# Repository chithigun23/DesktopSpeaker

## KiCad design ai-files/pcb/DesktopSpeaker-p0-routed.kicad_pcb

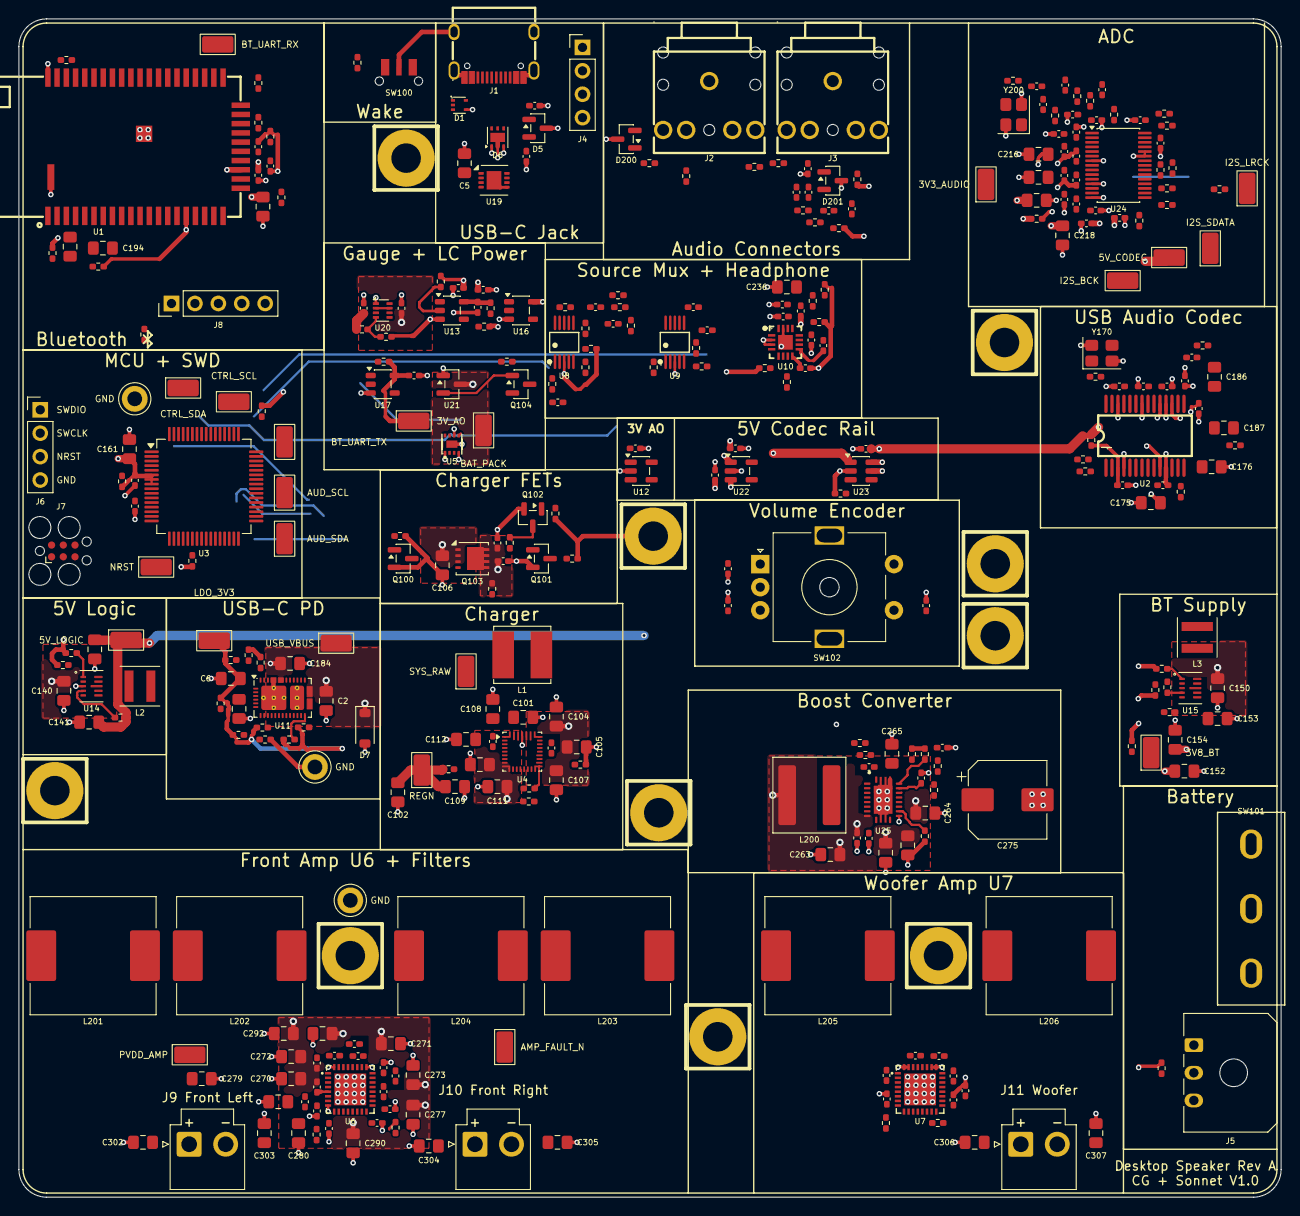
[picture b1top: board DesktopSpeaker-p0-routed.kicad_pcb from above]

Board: 4 copper layers, 136.9 x 127.8 mm, 351 parts (1 on the bottom side), 208 nets.

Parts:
C2, C5: 4.7uF X7R 50V; C_0805_2012Metric_Pad1.18x1.45mm_HandSolder
C6: 22uF X7R 10V; C_0805_2012Metric_Pad1.18x1.45mm_HandSolder
C100, C101, C108, C111, C112: 10uF / 50V; C_0805_2012Metric_Pad1.18x1.45mm_HandSolder
C102, C109: 10uF / 10V; C_0805_2012Metric_Pad1.18x1.45mm_HandSolder
C103, C110: 47nF / 50V; C_0402_1005Metric_Pad0.74x0.62mm_HandSolder
C104, C105, C106, C107: 22uF / 10V; C_0805_2012Metric_Pad1.18x1.45mm_HandSolder
C120: 100nF X7R 10V; C_0402_1005Metric_Pad0.74x0.62mm_HandSolder
C122, C123, C124, C125: 1uF X5R 16V; C_0402_1005Metric_Pad0.74x0.62mm_HandSolder
C126, C130, C131, C132, C160, C162, C191, C213, C215, C217, C219, C237, C238, C246, C260, C267, C276, C278, C281, C289, C291, C294: 100nF; C_0402_1005Metric_Pad0.74x0.62mm_HandSolder
C140, C141, C142, C150, C152, C153, C154: 22uF 10V X7R; C_0805_2012Metric_Pad1.18x1.45mm_HandSolder
C161, C186, C187, C194, C195, C236, C280, C293: 4.7uF; C_0805_2012Metric_Pad1.18x1.45mm_HandSolder
C170, C171, C172, C173, C174, C192, C193, C212, C220, C221, C222, C224, C225, C230, C231, C232, C233, C234, C235, C239, C240, C241, C245, C282, C283, C284, C295, C296, C297: 1uF; C_0402_1005Metric_Pad0.74x0.62mm_HandSolder
C175, C176, C190, C214, C216, C218, C223: 10uF; C_0805_2012Metric_Pad1.18x1.45mm_HandSolder
C177, C178: 33pF; C_0402_1005Metric_Pad0.74x0.62mm_HandSolder
C181: 10uF X7R 10V; C_0805_2012Metric_Pad1.18x1.45mm_HandSolder
C182: 330pF C0G CC1 filter; C_0402_1005Metric_Pad0.74x0.62mm_HandSolder
C183: 330pF C0G CC2 filter; C_0402_1005Metric_Pad0.74x0.62mm_HandSolder
C184: 1uF X7R 50V; C_0805_2012Metric_Pad1.18x1.45mm_HandSolder
C200, C201, C202, C203, C204, C205, C243, C244: 2.2uF; C_0402_1005Metric_Pad0.74x0.62mm_HandSolder
C206, C207, C208, C209, C210, C211: 10nF C0G; C_0402_1005Metric_Pad0.74x0.62mm_HandSolder
C226, C227: 22pF C0G; C_0402_1005Metric_Pad0.74x0.62mm_HandSolder
C261, C262, C263, C264: 22uF 10V; C_0805_2012Metric_Pad1.18x1.45mm_HandSolder
C265: 2.2uF; C_0805_2012Metric_Pad1.18x1.45mm_HandSolder
C266: 47nF; C_0402_1005Metric_Pad0.74x0.62mm_HandSolder
C268: 6.8nF; C_0402_1005Metric_Pad0.74x0.62mm_HandSolder
C269: 47pF; C_0402_1005Metric_Pad0.74x0.62mm_HandSolder
C270: 1uF; C_0805_2012Metric_Pad1.18x1.45mm_HandSolder
C271, C272, C273, C274, C277, C279, C290, C292: 22uF 25V; C_0805_2012Metric_Pad1.18x1.45mm_HandSolder
C275: 100uF 25V; CP_Elec_8x10
C285, C286, C287, C288, C298, C299, C300, C301: 0.47uF; C_0402_1005Metric_Pad0.74x0.62mm_HandSolder
C302, C303, C304, C305, C306, C307: 0.68uF 50V; C_0805_2012Metric_Pad1.18x1.45mm_HandSolder
C308, C309, C310: 10nF; C_0402_1005Metric_Pad0.74x0.62mm_HandSolder
D1: TPD2E2U06DRLR
D5: ESDA25L
D6: TVS2200DRVR
D7: 1N5819HW; PD_D_SOD123
D200, D201: PESD5V0S2BT
FB200: BLM15AG601SN1D; R_0402_1005Metric_Pad0.72x0.64mm_HandSolder
H1, H2, H3, H4, H5, H6, H7, H9: M3 PTH GND; MountingHole_3.2mm_M3_PTH_GND
HA1, HA2: M3 PTH GND; MountingHole_3.2mm_M3_PTH_GND
J1: USB_C_Receptacle_USB2.0_16P; TYPE-C-31-M-12
J2: HEAD_OUT; PJ-307
J3: AUX_IN; PJ-307
J4: I2C service; PD_SERVICE_HDR
J5: 1S_PACK_3PIN; Molex_Micro-Fit_3.0_43650-0300_1x03_P3.00mm_Horizontal
J6: SWD; PinHeader_1x04_P2.54mm_Vertical
J7: SWD_TC2030; Tag-Connect_TC2030-IDC-FP_2x03_P1.27mm_Vertical
J8: BM83_PROG; PinHeader_1x05_P2.54mm_Vertical
J9, J10, J11: B2P-VH; JST_B2P_VH_1x02_P3.96mm_Vertical
L1: 2.2uH; Bourns_SRN6045TA-2R2Y
L2, L3: 0.47uH; Coilcraft_XFL4015-471MEC
L200: 2.2uH; L_Coilcraft_XAL7070-XXX
L201, L202, L203, L204, L205, L206: 22uH; L_Sunlord_MWSA1265S
LOGO1: Orwellian Industries; Logo_Orwellian
Q100, Q101, Q102, Q104: 2N7002
Q103: CSD17579Q3A; CSD17579Q3A_DNH0008A
R10: 200k 1%; R_0402_1005Metric_Pad0.72x0.64mm_HandSolder
R11, R13, R14, R15, R18: 10k 1%; R_0402_1005Metric_Pad0.72x0.64mm_HandSolder
R12, R16, R17: 100k 1%; R_0402_1005Metric_Pad0.72x0.64mm_HandSolder
R100: 5.23k; R_0402_1005Metric_Pad0.72x0.64mm_HandSolder
R101: 30.1k; R_0402_1005Metric_Pad0.72x0.64mm_HandSolder
R102, R120, R121: 4.7k; R_0402_1005Metric_Pad0.72x0.64mm_HandSolder
R103, R107, R109, R110, R111, R113, R125, R142, R152, R153, R154, R160, R175, R176, R180, R181, R184, R211, R212, R220, R221, R222, R223, R224, R225, R234, R235, R236, R237, R238, R239, R255, R259: 100k; R_0402_1005Metric_Pad0.72x0.64mm_HandSolder
R106, R182, R183, R242, R243, R244, R262: 10k; R_0402_1005Metric_Pad0.72x0.64mm_HandSolder
R108, R124: 180k; R_0402_1005Metric_Pad0.72x0.64mm_HandSolder
R112: 100R; R_0402_1005Metric_Pad0.72x0.64mm_HandSolder
R122, R232, R233: 47k; R_0402_1005Metric_Pad0.72x0.64mm_HandSolder
R126, R127, R174, R241: 1M; R_0402_1005Metric_Pad0.72x0.64mm_HandSolder
R140: 78.7k 1%; R_0402_1005Metric_Pad0.72x0.64mm_HandSolder
R141: 9.1k 1%; R_0402_1005Metric_Pad0.72x0.64mm_HandSolder
R150: 604k 1%; R_0402_1005Metric_Pad0.72x0.64mm_HandSolder
R151: 91k 1%; R_0402_1005Metric_Pad0.72x0.64mm_HandSolder
R170: 2.2; R_0402_1005Metric_Pad0.72x0.64mm_HandSolder
R171, R172: 22; R_0402_1005Metric_Pad0.72x0.64mm_HandSolder
R173: 1.5k; R_0402_1005Metric_Pad0.72x0.64mm_HandSolder
R185, R186, R187, R226, R227, R228, R229, R230, R231, R240, R257, R258, R261: 1k; R_0402_1005Metric_Pad0.72x0.64mm_HandSolder
R200, R201, R202, R203, R204, R205: 100; R_0402_1005Metric_Pad0.72x0.64mm_HandSolder
R206, R207, R208: 33; R_0402_1005Metric_Pad0.72x0.64mm_HandSolder
R209, R210: 2.2k; R_0402_1005Metric_Pad0.72x0.64mm_HandSolder
R250: 499k; R_0402_1005Metric_Pad0.72x0.64mm_HandSolder
R251: 56k; R_0402_1005Metric_Pad0.72x0.64mm_HandSolder
R252: 301k; R_0402_1005Metric_Pad0.72x0.64mm_HandSolder
R253: 150k; R_0402_1005Metric_Pad0.72x0.64mm_HandSolder
R254: 82k; R_0402_1005Metric_Pad0.72x0.64mm_HandSolder
R256: 0R DNP; R_0402_1005Metric_Pad0.72x0.64mm_HandSolder
SW100: WAKE_QON; TE_1977066-1_Tact_RA_SMD
SW101: BAT_DISCONNECT; SHOUHAN_KCD1-201-R_Rocker_D20_Panel
SW102: EC11E; RotaryEncoder_Alps_EC11E-Switch_Vertical_H20mm_MountingHoles
TP1: USB_VBUS; TestPoint_Keystone_5015_Micro_Mini
TP2: SYS_RAW; TestPoint_Keystone_5015_Micro_Mini
TP3: BAT_PACK; TestPoint_Keystone_5015_Micro_Mini
TP4: 3V_AO; TestPoint_Keystone_5015_Micro_Mini
TP5: LDO_3V3; TestPoint_Keystone_5015_Micro_Mini
TP6: 3V3_AUDIO; TestPoint_Keystone_5015_Micro_Mini
TP7: 5V_LOGIC; TestPoint_Keystone_5015_Micro_Mini
TP8: 5V_CODEC; TestPoint_Keystone_5015_Micro_Mini
TP9: 3V8_BT; TestPoint_Keystone_5015_Micro_Mini
TP10: PVDD_AMP; TestPoint_Keystone_5015_Micro_Mini
TP11: REGN; TestPoint_Keystone_5015_Micro_Mini
TP12: I2S_BCK; TestPoint_Keystone_5015_Micro_Mini
TP13: I2S_LRCK; TestPoint_Keystone_5015_Micro_Mini
TP14: I2S_SDATA; TestPoint_Keystone_5015_Micro_Mini
TP15: CTRL_SDA; TestPoint_Keystone_5015_Micro_Mini
TP16: CTRL_SCL; TestPoint_Keystone_5015_Micro_Mini
TP17: AUD_SDA; TestPoint_Keystone_5015_Micro_Mini
TP18: AUD_SCL; TestPoint_Keystone_5015_Micro_Mini
TP19: NRST; TestPoint_Keystone_5015_Micro_Mini
TP20: AMP_FAULT_N; TestPoint_Keystone_5015_Micro_Mini
TP21: BT_UART_TX; TestPoint_Keystone_5015_Micro_Mini
TP22: BT_UART_RX; TestPoint_Keystone_5015_Micro_Mini
TP23, TP24, TP25: GND; TestPoint_Keystone_5010-5014_Multipurpose
U1: BM83SM1-00TA
U2: PCM2902CDBR
U3: STM32G071RBT6
U4: BQ25792RQMR
U5: MAX17048G+T10
U6, U7: TAS5825MRHBR
U8, U9: TS5A23157DGSR
U10: TPA6132A2RTER
U11: TPS25730DREFR; TPS25730D
U12: TPS7A0230PDBVR
U13, U16, U17: TS5A3167DBVR
U14, U15: TPS63802DLAR
U19: TPS7B8450QWDRBRQ1; TPS7B8450QWDRBRQ1_WSON-8
U20: TPS2116DRLR
U21: TPS3839G33DBZR
U22: TPS7A2033PDBVR
U23: TPS22917DBVR
U24: PCM1862DBTR
U25: TPS61088RHLR
Y170: 12MHz; Crystal_SMD_3225-4Pin_3.2x2.5mm
Y200: 24.576MHz; Crystal_SMD_3225-4Pin_3.2x2.5mm

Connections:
/3V3_AUDIO: C217.1, C218.1, C219.1, C220.1, C222.1, C223.1, C237.1, C238.1, C241.1, C280.1, C281.1, C293.1, C294.1, FB200.1, R209.1, R210.1, R232.1, R239.1, R262.1, TP6.1, U6.6, U7.6, U8.8, U9.8, U10.14, U22.5, U24.13, U24.14
/3V8_BT: C152.1, C153.1, C154.1, C190.1, C191.1, R150.1, R154.1, TP9.1, U1.23, U15.6
/3V_AO: C123.1, C130.1, C131.1, C132.1, C160.1, C161.1, J7.1, R106.1, R120.1, R121.1, R122.1, R126.1, R241.1, TP4.1, U3.6, U3.7, U3.8, U12.5, U13.5, U16.5, U17.5
/5V_CODEC: C225.1, R170.1, TP8.1, U23.5, U23.6
/5V_LOGIC: C141.1, C142.1, C221.1, C224.1, R140.1, TP7.1, U14.6, U22.1, U22.3, U23.1
/5V_LOGIC_EN: R142.1, U3.59, U14.1
/ADC_INT: R211.1, U3.26, U24.21
/AMP_BOOST_EN: R255.1, U3.24, U25.2
/AMP_FAULT_N: R262.2, TP20.1, U3.25, U6.9, U7.9
/AMP_PDN: R257.1, R258.1, R259.1, U3.23
/AUD_SCL: R209.2, TP18.1, U3.30, U6.16, U7.16, U24.24
/AUD_SDA: R210.2, TP17.1, U3.31, U6.15, U7.15, U24.23
/AUX_DET: R242.2, U3.29
/AUX_L: C204.1, C234.1, D201.1, J3.5, R243.1
/AUX_R: C205.1, C235.1, D201.2, J3.2, R244.1
/Amplifiers/PVDD_AMP: C270.1, C271.1, C272.1, C273.1, C274.1, C275.1, C276.1, C277.1, C278.1, C279.1, C289.1, C290.1, C291.1, C292.1, R250.1, TP10.1, U6.3, U6.4, U6.21, U6.22, U7.3, U7.4, U7.21, U7.22, U25.14, U25.15, U25.16
/BT_AUDIO_L: C194.2, C202.1, C232.1, R180.1
/BT_AUDIO_R: C195.2, C203.1, C233.1, R181.1
/BT_FORCE_PWM: R153.1, U3.37, U15.2
/BT_MFB: R183.1, U3.57
/BT_PWR_EN: R152.1, U3.36, U15.1
/BT_RST_N: R185.1, U3.58
/BT_TX_IND: R187.2, U3.62
/BT_UART_RX: R186.2, TP22.1, U3.20
/BT_UART_TX: R182.1, TP21.1, U3.19
/Battery_Charger/BAT_INT: C106.1, Q103.1, Q103.2, Q103.3, U4.22, U4.23
/Battery_Charger/BTST1: C103.1, U4.4
/Battery_Charger/BTST2: C110.1, U4.19
/Battery_Charger/CE_N: Q100.3, R103.2, U4.13
/Battery_Charger/ILIM_HIZ: Q101.3, R108.2, R109.1, U4.17
/Battery_Charger/PACK_RAW: J5.1, SW101.2
/Battery_Charger/PMID: C101.1, C108.1, C112.1, U4.29
/Battery_Charger/PROG: R102.1, U4.20
/Battery_Charger/REGN: C102.1, C109.1, R100.1, R103.1, R108.1, R110.1, TP11.1, U4.5
/Battery_Charger/SW1: C103.2, L1.1, U4.28
/Battery_Charger/SW2: C110.2, L1.2, U4.26
/Battery_Charger/TS_SENSE: J5.2, R100.2, R101.1, U4.16
/Battery_Charger/VBUS_PD: C100.1, C111.1, U4.2, U4.3, U4.8, U4.9, U11.20
/Bluetooth/BT_RST_M: J8.1, R185.2, U1.43
/Bluetooth/BT_RXD_M: J8.3, R182.2, U1.29
/Bluetooth/BT_SYS_CFG: J8.2, U1.31
/Bluetooth/BT_TXD_M: J8.4, R186.1, U1.30
/CHG_ENABLE: Q100.1, R107.1, U3.38
/CHG_INT: R106.2, U3.5, U4.21
/CHG_QON_SENSE: R113.2, U3.3
/CHG_SYS_ENABLE: Q102.1, R111.1, U3.42
/CODEC_PWR_EN: R212.1, U3.39, U23.3
/CTRL_SCL: R120.2, TP16.1, U3.60, U4.14, U16.2
/CTRL_SDA: R121.2, TP15.1, U3.61, U4.15, U13.2
/Fuel_Gauge_Power/BAT_PACK: C120.1, C126.1, Q103.5, Q103.6, Q103.7, Q103.8, Q103.9, R112.1, SW101.1, TP3.1, U5.3, U21.3
/Fuel_Gauge_Power/GAUGE_ISO_N: Q104.3, R126.2, U13.4, U16.4, U17.4
/Fuel_Gauge_Power/USB_AUX_5V: C5.1, C124.1, R124.1, U19.1, U20.3, U20.5
/GAUGE_ALRT_N: R122.2, U3.17, U17.2
/HP_DET: R240.2, U3.28
/HP_EN: R236.1, U3.15, U10.13
/HP_G0: R237.1, U3.16, U10.6
/HP_G1: R238.1, U3.21, U10.7
/HP_SEL_A: R234.1, U3.13, U8.1, U8.5
/HP_SEL_B: R235.1, U3.14, U9.1, U9.5
/Headphone_Aux/AUX_TIPSW: C246.1, J3.4, R241.2, R242.1
/Headphone_Aux/HP_L: C239.1, U9.10
/Headphone_Aux/HP_OUTL: D200.1, J2.5, U10.16
/Headphone_Aux/HP_OUTR: D200.2, J2.2, U10.5
/Headphone_Aux/HP_R: C240.1, U9.6
/Headphone_Aux/HP_TIPSW: J2.4, R239.2, R240.1
/Headphone_Aux/VMID_HP: C236.1, R220.2, R221.2, R222.2, R223.2, R224.2, R225.2, R232.2, R233.1
/I2S_BCK: R207.2, TP12.1, U6.13, U7.13
/I2S_LRCK: R208.2, TP13.1, U6.12, U7.12
/I2S_SDATA: R206.2, TP14.1, U6.14, U7.14
/MCU/ENC_A: C308.1, SW102.A, U3.48
/MCU/ENC_B: C309.1, SW102.B, U3.49
/MCU/ENC_SW: C310.1, SW102.S1, U3.64
/MCU/NRST: C162.1, J6.3, J7.3, TP19.1, U3.12
/MCU/SWCLK: J6.2, J7.4, R160.1, U3.46
/MCU/SWDIO: J6.1, J7.2, U3.45
/PDCTRL_SCL: J4.2, R15.2, U3.43, U11.9
/PDCTRL_SDA: J4.3, R14.2, U3.44, U11.8
/PD_PLUG_EVENT: R16.1, U3.4, U11.37
/PD_SINK_EN: R17.2, U3.63, U11.19
/SYS_RAW: C104.1, C105.1, C107.1, C125.1, C140.1, C150.1, C260.1, C261.1, C262.1, C263.1, C264.1, L200.1, TP2.1, U4.25, U14.2, U14.10, U15.10, U20.6, U25.9
/USB_AUDIO_L: C186.2, C200.1, C230.1, R175.1
/USB_AUDIO_R: C187.2, C201.1, C231.1, R176.1
/USB_CC1: C182.1, D5.1, J1.A5, U11.28
/USB_CC2: C183.1, D5.2, J1.B5, U11.29
/USB_DN: D1.5, J1.A7, J1.B7, R172.1
/USB_DP: D1.3, J1.A6, J1.B6, R171.1, R173.1
/USB_PD/LDO_1V5: C181.1, U11.4
/USB_PD/LDO_3V3: C6.1, J4.1, R10.1, R13.1, R14.1, R15.1, R16.2, R17.1, TP5.1, U11.1, U11.3
/USB_PD/VIN_LOW: R12.1, U11.38
/USB_VBUS: C2.1, C184.1, D6.4, D6.5, D6.6, D7.1, J1.A4B9, J1.B4A9, TP1.1, U11.23, U11.32, U19.7, U19.8
GND: C2.2, C5.2, C6.2, C100.2, C101.2, C102.2, C104.2, C105.2, C106.2, C107.2, C108.2, C109.2, C111.2, C112.2, C120.2, C122.2, C123.2, C124.2, C125.2, C126.2, C130.2, C131.2, C132.2, C140.2, C141.2, C142.2, C150.2, C152.2, C153.2, C154.2, C160.2, C161.2, C162.2, C170.2, C171.2, C172.2, C173.2, C174.2, C175.2, C176.2, C177.2, C178.2, C181.2, C182.2, C183.2, C184.2, C190.2, C191.2, C192.2, C193.2, C206.2, C207.2, C208.2, C209.2, C210.2, C211.2, C212.2, C213.2, C214.2, C215.2, C216.2, C217.2, C218.2, C219.2, C220.2, C221.2, C222.2, C223.2, C224.2, C225.2, C226.2, C227.2, C236.2, C237.2, C238.2, C241.2, C243.2, C244.2, C246.2, C260.2, C261.2, C262.2, C263.2, C264.2, C265.2, C266.2, C268.2, C269.2, C270.2, C271.2, C272.2, C273.2, C274.2, C275.2, C276.2, C277.2, C278.2, C279.2, C280.2, C281.2, C282.2, C283.2, C284.2, C289.2, C290.2, C291.2, C292.2, C293.2, C294.2, C295.2, C296.2, C297.2, C302.2, C303.2, C304.2, C305.2, C306.2, C307.2, C308.2, C309.2, C310.2, D1.4, D5.3, D6.1, D6.2, D6.3, D6.7, D7.2, D200.3, D201.3, H1.1, H2.1, H3.1, H4.1, H5.1, H6.1, H7.1, H9.1, HA1.1, HA2.1, J1.1, J1.2, J1.3, J1.4, J1.A1B12, J1.B1A12, J2.1, J3.1, J4.4, J5.3, J6.4, J7.5, J8.5, Q100.2, Q101.2, Q102.2, Q104.2, R11.2, R12.2, R18.2, R101.2, R102.2, R107.2, R109.2, R111.2, R125.2, R127.2, R141.2, R142.2, R151.2, R152.2, R153.2, R154.2, R160.2, R175.2, R176.2, R180.2, R181.2, R184.2, R211.2, R212.2, R233.2, R234.2, R235.2, R236.2, R237.2, R238.2, R243.2, R244.2, R251.2, R253.2, R255.2, R256.2, R259.2, R261.1, SW100.2, SW102.C, SW102.MP, SW102.S2, TP23.1, TP24.1, TP25.1, U1.16, U1.50, U1.56, U1.57, U2.4, U2.11, U2.18, U2.22, U2.26, U3.9, U4.10, U4.11, U4.27, U5.1, U5.4, U5.6, U5.9, U6.5, U6.8, U6.20, U6.25, U6.26, U6.31, U6.32, U6.33, U7.5, U7.20, U7.25, U7.26, U7.31, U7.32, U7.33, U8.3, U9.3, U10.2, U10.3, U10.10, U10.15, U10.17, U11.2, U11.5, U11.11, U11.12, U11.14, U11.16, U11.17, U11.26, U11.27, U11.31, U11.34, U11.39, U12.2, U13.3, U14.3, U14.8, U15.3, U15.8, U16.3, U17.3, U19.5, U19.9, U20.1, U21.1, U22.2, U23.2, U24.7, U24.12, U24.15, U24.25, U24.26, U25.11, U25.12, U25.20, U25.21, Y170.2, Y170.4, Y200.2, Y200.4
unnamed: C200.2, R200.1
unnamed: C201.2, R201.1
unnamed: C202.2, R202.1
unnamed: C203.2, R203.1
unnamed: C204.2, R204.1
unnamed: C205.2, R205.1
unnamed: C230.2, R220.1, R226.1
unnamed: C231.2, R221.1, R227.1
unnamed: C232.2, R222.1, R228.1
unnamed: C233.2, R223.1, R229.1
unnamed: C234.2, R224.1, R230.1
unnamed: C235.2, R225.1, R231.1
unnamed: C268.1, R254.2
unnamed: C302.1, J9.1, L201.2
unnamed: C303.1, J9.2, L202.2
unnamed: C304.1, J10.1, L203.2
unnamed: C305.1, J10.2, L204.2
unnamed: C306.1, J11.1, L205.2
unnamed: C307.1, J11.2, L206.2
unnamed: Q101.1, Q102.3, R110.2
unnamed: Q103.4, U4.24
unnamed: Q104.1, R127.1, U21.2
unnamed: R18.1, U11.36
unnamed: C194.1, U1.8
unnamed: C195.1, U1.6
unnamed: R187.1, U1.49
unnamed: R183.2, R184.1, U1.26
unnamed: C193.1, U1.24
unnamed: C192.1, U1.25
unnamed: R171.2, U2.1
unnamed: R172.2, U2.2
unnamed: C171.1, R173.2, U2.8, U2.9, U2.27
unnamed: C170.1, R170.2, U2.3
unnamed: C175.1, U2.10
unnamed: C174.1, U2.17
unnamed: C173.1, U2.19
unnamed: C172.1, U2.23
unnamed: C176.1, U2.14
unnamed: C186.1, U2.16
unnamed: C187.1, U2.15
unnamed: C177.1, R174.1, U2.21, Y170.1
unnamed: C178.1, R174.2, U2.20, Y170.3
unnamed: R112.2, U4.18
unnamed: R113.1, SW100.1, U4.12
unnamed: C284.1, U6.19
unnamed: C285.1, U6.1
unnamed: C286.2, U6.29
unnamed: C287.1, U6.24
unnamed: C288.2, U6.28
unnamed: C283.1, U6.18
unnamed: C285.2, L201.1, U6.2
unnamed: C286.1, L202.1, U6.30
unnamed: C287.2, L203.1, U6.23
unnamed: C288.1, L204.1, U6.27
unnamed: C282.1, U6.7
unnamed: R257.2, U6.17
unnamed: R261.2, U7.8
unnamed: C297.1, U7.19
unnamed: C298.1, U7.1
unnamed: C299.2, U7.29
unnamed: C300.1, U7.24
unnamed: C301.2, U7.28
unnamed: C296.1, U7.18
unnamed: C298.2, C299.1, L205.1, U7.2, U7.30
unnamed: C300.2, C301.1, L206.1, U7.23, U7.27
unnamed: C295.1, U7.7
unnamed: R258.2, U7.17
unnamed: U8.10, U9.9
unnamed: U8.6, U9.7
unnamed: R226.2, U8.9
unnamed: R227.2, U8.7
unnamed: R228.2, U8.2
unnamed: R229.2, U8.4
unnamed: R230.2, U9.2
unnamed: R231.2, U9.4
unnamed: C245.2, U10.9
unnamed: C245.1, U10.11
unnamed: C243.1, U10.12
unnamed: C244.1, U10.8
unnamed: C239.2, U10.1
unnamed: C240.2, U10.4
unnamed: R10.2, R11.1, U11.7
unnamed: R13.2, U11.18
unnamed: C122.1, U12.1, U12.3, U20.2, U20.7
unnamed: U5.8, U13.1
unnamed: R140.2, R141.1, U14.4
unnamed: L2.1, U14.9
unnamed: L2.2, U14.7
unnamed: R150.2, R151.1, U15.4
unnamed: L3.1, U15.9
unnamed: L3.2, U15.7
unnamed: U5.7, U16.1
unnamed: U5.5, U17.1
unnamed: R124.2, R125.1, U20.4
unnamed: C215.1, C216.1, FB200.2, U24.8
unnamed: R207.1, U24.17
unnamed: R206.1, U24.18
unnamed: C213.1, C214.1, U24.11
unnamed: R208.1, U24.16
unnamed: C206.1, R200.2, U24.3
unnamed: C208.1, R202.2, U24.1
unnamed: C210.1, R204.2, U24.29
unnamed: C207.1, R201.2, U24.4
unnamed: C209.1, R203.2, U24.2
unnamed: C211.1, R205.2, U24.30
unnamed: C212.1, U24.6
unnamed: C226.1, U24.10, Y200.1
unnamed: C227.1, U24.9, Y200.3
unnamed: C267.1, U25.8
unnamed: C269.1, R254.1, U25.18
unnamed: R250.2, R251.1, U25.17
unnamed: R252.1, U25.3
unnamed: R253.1, U25.19
unnamed: R256.1, U25.13
unnamed: C266.1, U25.10
unnamed: C267.2, L200.2, R252.2, U25.4, U25.5, U25.6, U25.7
unnamed: C265.1, U25.1

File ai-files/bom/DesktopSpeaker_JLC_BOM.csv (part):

Comment,Designator,Footprint,LCSC Part #,MPN,Manufacturer,Qty
4.7uF X7R 50V,"C2,C5",C_0805_2012Metric_Pad1.18x1.45mm_HandSolder,C5159426,C2012X7R1H475KT0A0E,TDK,2
22uF 10V X7R,"C6,C104,C105,C106,C107,C140,C141,C142,C150,C152,C153,C154,C261,C262,C263,C264",C_0805_2012Metric_Pad1.18x1.45mm_HandSolder,C907991,GRM21BZ71A226ME15L,Murata,16
10uF / 50V,"C100,C101,C108,C111,C112",C_0805_2012Metric_Pad1.18x1.45mm_HandSolder,C440198,GRM21BR61H106KE43L,Murata,5
10uF,"C102,C109,C175,C176,C181,C190,C214,C216,C218,C223",C_0805_2012Metric_Pad1.18x1.45mm_HandSolder,C32635,CL21B106KPQNNNE,Samsung Electro-Mechanics,10
47nF / 50V,"C103,C110,C266",C_0402_1005Metric_Pad0.74x0.62mm_HandSolder,C117757,GRM155R71H473KE14D,Murata,3
100nF,"C120,C126,C130,C131,C132,C160,C162,C191,C213,C215,C217,C219,C237,C238,C246,C260,C267,C276,C278,C281,C289,C291,C294,C311,C312,C313,C314",C_0402_1005Metric_Pad0.74x0.62mm_HandSolder,C77020,GRM155R71H104KE14D,Murata,27
1uF,"C122,C123,C124,C125,C170,C171,C172,C173,C174,C192,C193,C212,C220,C221,C222,C224,C225,C230,C231,C232,C233,C234,C235,C239,C240,C245,C282,C283,C284,C295,C296,C297",C_0402_1005Metric_Pad0.74x0.62mm_HandSolder,C29266,CL05A105KO5NNNC,Samsung Electro-Mechanics,32
4.7uF,"C161,C186,C187,C194,C195,C236,C280,C293",C_0805_2012Metric_Pad1.18x1.45mm_HandSolder,C1779,CL21A475KAQNNNE,Samsung Electro-Mechanics,8
33pF,"C177,C178",C_0402_1005Metric_Pad0.74x0.62mm_HandSolder,C5137486,FCC0402N330J500AT,FOJAN,2
330pF C0G CC1 filter,"C182,C183",C_0402_1005Metric_Pad0.74x0.62mm_HandSolder,C76965,GRM1555C1H331JA01D,Murata,2
1uF X7R 50V,"C184,C270,C316",C_0805_2012Metric_Pad1.18x1.45mm_HandSolder,C28323,CL21B105KBFNNNE,Samsung Electro-Mechanics,3
2.2uF,"C200,C201,C202,C203,C204,C205,C241,C243,C244",C_0402_1005Metric_Pad0.74x0.62mm_HandSolder,C7464343,CL05A225KP5NNNC,Samsung Electro-Mechanics,9
10nF C0G,"C206,C207,C208,C209,C210,C211",C_0402_1005Metric_Pad0.74x0.62mm_HandSolder,C22400107,GRM1555C1H103JE01D,Murata,6
15pF C0G,"C226,C227",C_0402_1005Metric_Pad0.74x0.62mm_HandSolder,C76950,GRM1555C1H150JA01D,Murata,2
2.2uF,C265,C_0805_2012Metric_Pad1.18x1.45mm_HandSolder,C19110,CL21B225KAFNNNE,Samsung Electro-Mechanics,1
6.8nF,C268,C_0402_1005Metric_Pad0.74x0.62mm_HandSolder,C318580,CL05B682KB5NNNC,Samsung Electro-Mechanics,1
47pF,C269,C_0402_1005Metric_Pad0.74x0.62mm_HandSolder,C76970,GRM1555C1H470JA01D,Murata,1
22uF 25V,"C271,C272,C273,C274,C277,C279,C290,C292",C_0805_2012Metric_Pad1.18x1.45mm_HandSolder,C45783,CL21A226MAQNNNE,Samsung Electro-Mechanics,8
100uF 25V,C275,CP_Elec_8x10,C264047,EEHZA1E101XP,Panasonic,1
0.47uF,"C285,C286,C287,C288,C298,C299,C300,C301",C_0402_1005Metric_Pad0.74x0.62mm_HandSolder,C22435970,CGA0402X7R474K160GT,HRE,8
0.68uF 50V,"C302,C303,C304,C305,C306,C307",C_0805_2012Metric_Pad1.18x1.45mm_HandSolder,C472832,CL21B684KBFVPNE,Samsung Electro-Mechanics,6
10nF,"C308,C309,C310",C_0402_1005Metric_Pad0.74x0.62mm_HandSolder,C77019,GRM155R71H103KA88D,Murata,3
47uF 25V,C315,PD_C_1206,C403725,GRM31CR61E476ME44L,Murata,1
TPD2E2U06DRLR,D1,TPD2E2U06DRLR,C1972959,TPD2E2U06DRLR,Texas Instruments,1
ESDA25L,D5,ESDA25L,C95343,ESDA25L,STMicroelectronics,1
TVS2200DRVR,D6,TVS2200DRVR,C523793,TVS2200DRVR,Texas Instruments,1
1N5819HW,D7,PD_D_SOD123,C82544,1N5819HW-7-F,Diodes Incorporated,1
PESD5V0S2BT,"D200,D201",PESD5V0S2BT,C5380400,PESD5V0S2BT,DOWO,2
BLM15AG601SN1D,FB200,R_0402_1005Metric_Pad0.72x0.64mm_HandSolder,C76884,BLM15AG601SN1D,Murata,1
USB_C_Receptacle_USB2.0_16P,J1,TYPE-C-31-M-12,C165948,TYPE-C-31-M-12,Korean Hroparts,1
HEAD_OUT,"J2,J3",PJ-307,C2939173,PJ-307,HOOYA,2
I2C service,J4,PD_SERVICE_HDR,C124378,B-2100S04P-A110,Ckmtw,1
1S_PACK_3PIN,J5,Molex_Micro-Fit_3.0_43650-0300_1x03_P3.00mm_Horizontal,C503478,43650-0300,Molex,1
SWD,J6,PinHeader_1x04_P2.54mm_Vertical,C124378,B-2100S04P-A110,Ckmtw,1
BM83_PROG,J8,PinHeader_1x05_P2.54mm_Vertical,C54110162,XY-MTP254-1X5,XYECONN,1
B2P-VH,"J9,J10,J11",JST_B2P_VH_1x02_P3.96mm_Vertical,C160315,B2P-VH(LF)(SN),JST,3
2.2uH,L1,Bourns_SRN6045TA-2R2Y,C1332316,SRN6045TA-2R2Y,Bourns,1
0.47uH,"L2,L3",Coilcraft_XFL4015-471MEC,C18221164,XFL4015-471MEC,Coilcraft,2
2.2uH,L200,L_Coilcraft_XAL7070-XXX,C3911470,XAL7070-222MEC,Coilcraft,1
22uH,"L201,L202,L203,L204,L205,L206",L_Sunlord_MWSA1265S,C7245133,MWSA1265S-220MT,Sunlord,6
2N7002,"Q100,Q101,Q102,Q104",2N7002,C65189,"2N7002,215",Nexperia,4
CSD17579Q3A,Q103,CSD17579Q3A_DNH0008A,C97376,CSD17579Q3A,Texas Instruments,1
200k 1%,R10,R_0402_1005Metric_Pad0.72x0.64mm_HandSolder,C114763,RC0402FR-07200KL,Yageo,1
10k,"R11,R13,R14,R15,R18,R106,R182,R183,R242,R243,R244,R262",R_0402_1005Metric_Pad0.72x0.64mm_HandSolder,C60490,RC0402FR-0710KL,Yageo,12
100k,"R12,R16,R17,R103,R107,R109,R110,R111,R113,R125,R142,R152,R153,R154,R160,R175,R176,R180,R181,R184,R211,R212,R220,R221,R222,R223,R224,R225,R234,R235,R236,R237,R238,R239,R255,R259",R_0402_1005Metric_Pad0.72x0.64mm_HandSolder,C60491,RC0402FR-07100KL,Yageo,36
5.23k,R100,R_0402_1005Metric_Pad0.72x0.64mm_HandSolder,C25907,0402WGF5231TCE,UNI-ROYAL,1
30.1k,R101,R_0402_1005Metric_Pad0.72x0.64mm_HandSolder,C226982,AC0402FR-0730K1L,Yageo,1
4.7k,"R102,R120,R121",R_0402_1005Metric_Pad0.72x0.64mm_HandSolder,C105871,RC0402FR-074K7L,Yageo,3
180k,"R108,R124",R_0402_1005Metric_Pad0.72x0.64mm_HandSolder,C138046,RC0402FR-07180KL,Yageo,2
100,"R112,R200,R201,R202,R203,R204,R205",R_0402_1005Metric_Pad0.72x0.64mm_HandSolder,C106232,RC0402FR-07100RL,Yageo,7
47k,"R122,R232,R233",R_0402_1005Metric_Pad0.72x0.64mm_HandSolder,C93943,RC0402FR-0747KL,Yageo,3
1M,"R126,R127,R174,R241",R_0402_1005Metric_Pad0.72x0.64mm_HandSolder,C138033,RC0402FR-071ML,Yageo,4
78.7k 1%,R140,R_0402_1005Metric_Pad0.72x0.64mm_HandSolder,C163454,RC0402FR-0778K7L,Yageo,1
9.1k 1%,R141,R_0402_1005Metric_Pad0.72x0.64mm_HandSolder,C163450,RC0402FR-079K1L,Yageo,1
604k 1%,R150,R_0402_1005Metric_Pad0.72x0.64mm_HandSolder,C27013,0402WGF6043TCE,UNI-ROYAL,1
91k 1%,R151,R_0402_1005Metric_Pad0.72x0.64mm_HandSolder,C144733,AC0402FR-0791KL,Yageo,1
2.2,R170,R_0402_1005Metric_Pad0.72x0.64mm_HandSolder,C327251,RC0402FR-072R2L,Yageo,1
22,"R171,R172",R_0402_1005Metric_Pad0.72x0.64mm_HandSolder,C114765,RC0402FR-0722RL,Yageo,2
1.5k,R173,R_0402_1005Metric_Pad0.72x0.64mm_HandSolder,C114759,RC0402FR-071K5L,Yageo,1
1k,"R185,R186,R187,R226,R227,R228,R229,R230,R231,R240,R257,R258,R261",R_0402_1005Metric_Pad0.72x0.64mm_HandSolder,C106235,RC0402FR-071KL,Yageo,13
33,"R206,R207,R208",R_0402_1005Metric_Pad0.72x0.64mm_HandSolder,C138002,RC0402FR-0733RL,Yageo,3
2.2k,"R209,R210",R_0402_1005Metric_Pad0.72x0.64mm_HandSolder,C114762,RC0402FR-072K2L,Yageo,2
499k,R250,R_0402_1005Metric_Pad0.72x0.64mm_HandSolder,C137971,RC0402FR-07499KL,Yageo,1
56k,R251,R_0402_1005Metric_Pad0.72x0.64mm_HandSolder,C114756,RC0402FR-0756KL,Yageo,1
301k,R252,R_0402_1005Metric_Pad0.72x0.64mm_HandSolder,C171693,RC0402FR-07301KL,Yageo,1
150k,R253,R_0402_1005Metric_Pad0.72x0.64mm_HandSolder,C93947,RC0402FR-07150KL,Yageo,1
82k,R254,R_0402_1005Metric_Pad0.72x0.64mm_HandSolder,C144735,AC0402FR-0782KL,Yageo,1
WAKE_QON,SW100,TE_1977066-1_Tact_RA_SMD,C2972219,1977066-1,TE Connectivity,1
EC11E,SW102,RotaryEncoder_Alps_EC11E-Switch_Vertical_H20mm_MountingHoles,C370970,EC11E15244G1,Alps Alpine,1
BM83SM1-00TA,U1,BM83SM1-00TA,C6752723,BM83SM1-00TA,Microchip,1
PCM2902CDBR,U2,PCM2902CDBR,C2651869,PCM2902CDBR,Texas Instruments,1
STM32G071RBT6,U3,STM32G071RBT6,C432213,STM32G071RBT6,STMicroelectronics,1
BQ25792RQMR,U4,BQ25792RQMR,C2862876,BQ25792RQMR,Texas Instruments,1
MAX17048G+T10,U5,MAX17048G+T10,C2682616,MAX17048G+T10,Analog Devices,1
TAS5825MRHBR,"U6,U7",TAS5825MRHBR,C471049,TAS5825MRHBR,Texas Instruments,2
TS5A23157DGSR,"U8,U9",TS5A23157DGSR,C11133,TS5A23157DGSR,Texas Instruments,2
TPA6132A2RTER,U10,TPA6132A2RTER,C69901,TPA6132A2RTER,Texas Instruments,1
TPS25730DREFR,U11,TPS25730D,C22438973,TPS25730DREFR,Texas Instruments,1
TPS7A0230PDBVR,U12,TPS7A0230PDBVR,C3747031,TPS7A0230PDBVR,Texas Instruments,1
TS5A3167DBVR,"U13,U16,U17",TS5A3167DBVR,C128416,TS5A3167DBVR,Texas Instruments,3
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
